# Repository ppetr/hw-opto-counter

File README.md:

# Universal IR optical, directional proximity detector/counter with TWI (I²C) interface

_*Disclaimer:* This is not an officially supported Google product._

The board uses two IR LEDs with a modulated signal (both either 38KHz or 56KHz,
depending on the receiver type) whose light reflects off objects in front of
the device into an IR receiver.

Using two LEDs allows to determine an approximate position (or direction of
movement) of an object in one dimension. Modulating the signal significantly
reduces interference from natural IR light sources.

The microcontroller
([ATtiny3224](https://www.microchip.com/en-us/product/attiny3224)) varies the
signal strength to compute the strength of the reflected signal using the
[binary search
algorithm](https://en.wikipedia.org/wiki/Binary_search_algorithm).

The measured values are made available through I²C (subordinate).

## Event counter

In addition to reporting current values of reflections from both LEDs, the
microcontroller also counts the number of times the reflection quickly changes
(which we call "events"). These events are defined using two parameters:

- [Exponential moving
  average](https://en.wikipedia.org/wiki/Exponential_smoothing) smoothing
  factor ("half-life"), which computes the baseline signal to compare against.
  The default value is half-life of 10s.
- Delta factor \[0..1\]. An event is triggered when the signal differs more
  than the delta factor from its exponential moving average.

There are the following event types that are counted independently:

1. Signal reflected from LED1 crosses the delta boundary and returns while
   LED2's signal remained within.
   ```
   LED1:  ___|‾‾‾|___
   LED2:  ___________
   ```
2. Similarly the other way around.
3. LED1's signal crossed outside the delta boundary followed by LED2's signal
   crossing outside. This captures the situation when an object is moving in
   the direction LED1->LED2.
   ```
   LED1:  __|‾‾‾|____
   LED2:  ____|‾‾‾|__
   ```
4. Similarly the other way around.

## Status

Development of a prototype.

## Contributions

Please see [Code of Conduct](docs/code-of-conduct.md) and [Contributing](docs/contributing.md).

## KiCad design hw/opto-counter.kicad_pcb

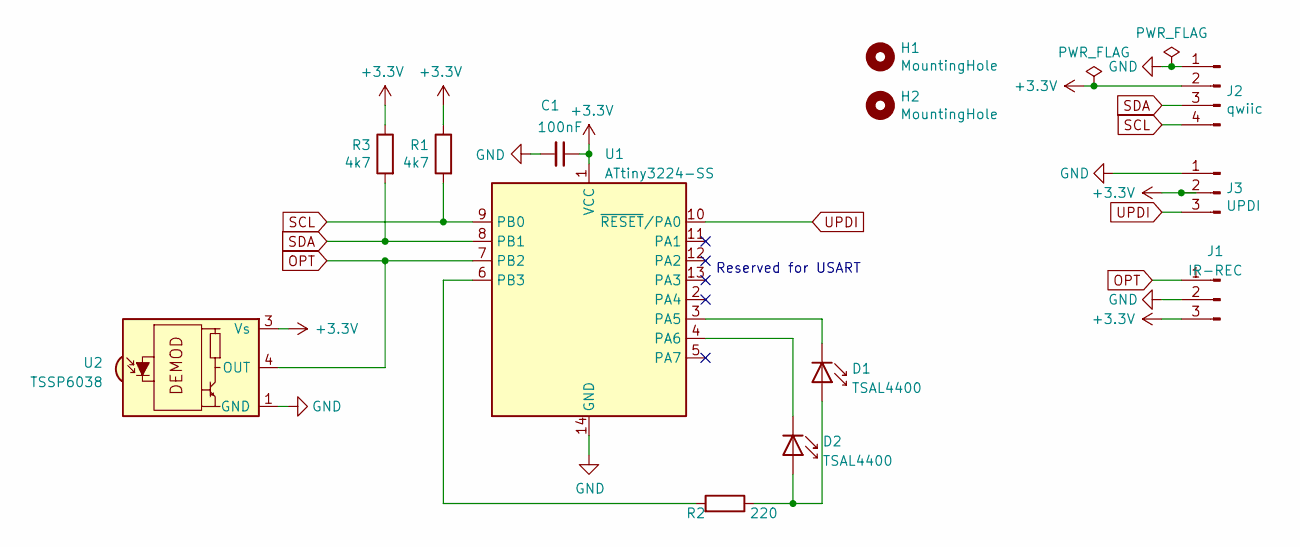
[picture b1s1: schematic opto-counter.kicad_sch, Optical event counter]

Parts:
C1: 100nF; C_1206_3216Metric_Pad1.33x1.80mm_HandSolder
D1, D2: TSAL4400; LED_D3.0mm_IRBlack
H1, H2: MountingHole; MountingHole_2.2mm_M2
J1: IR-REC; PinHeader_1x03_P2.54mm_Vertical
J2: qwiic; JST_XH_S4B-XH-A_1x04_P2.50mm_Horizontal
J3: UPDI; JST_XH_S3B-XH-A_1x03_P2.50mm_Horizontal
R1, R3: 4k7; R_1206_3216Metric_Pad1.30x1.75mm_HandSolder
R2: 220; R_1206_3216Metric_Pad1.30x1.75mm_HandSolder
U1: ATtiny3224-SS; SOIC-14_3.9x8.7mm_P1.27mm
U2: TSSP6038; TSS60xx

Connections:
+3V3: C1.1, J1.3, J2.2, J3.2, R1.1, R3.1, U1.1 (VCC), U2.3 (Vs)
GND: C1.2, J1.2, J2.1, J3.1, U1.14 (GND), U2.1 (GND)
unnamed: D1.2 (A), D2.2 (A), R2.1
unnamed: D1.1 (K), U1.3 (PA5)
unnamed: D2.1 (K), U1.4 (PA6)
unnamed: R2.2, U1.6 (PB3)
OPT: J1.1, U1.7 (PB2), U2.4 (OUT)
SCL: J2.4, R1.2, U1.9 (PB0)
SDA: J2.3, R3.2, U1.8 (PB1)
UPDI: J3.3, U1.10 (~RESET/PA0)

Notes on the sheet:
Reserved for USART

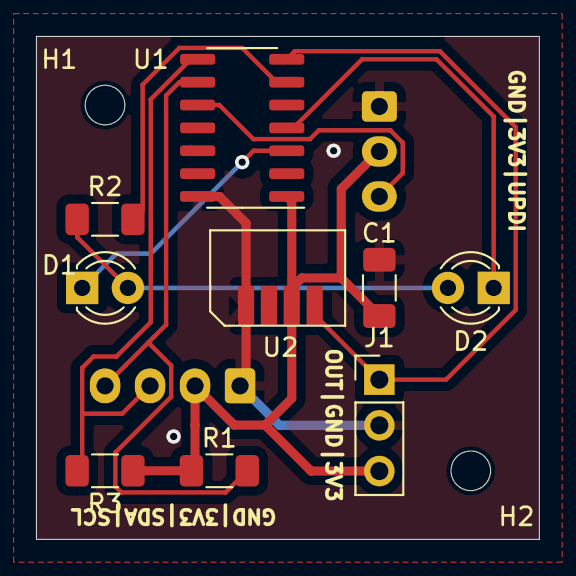
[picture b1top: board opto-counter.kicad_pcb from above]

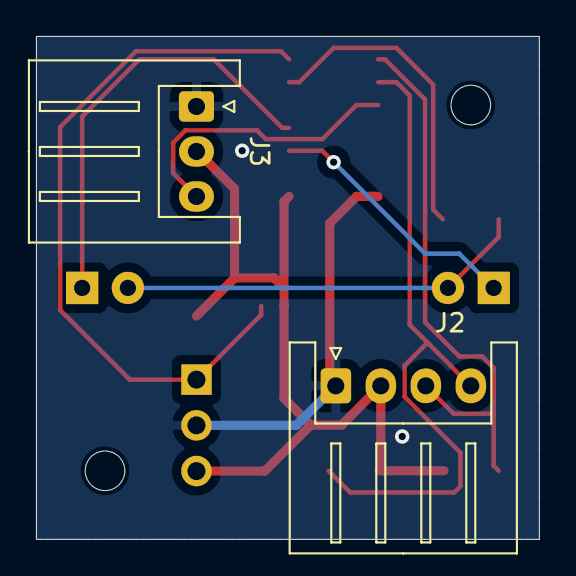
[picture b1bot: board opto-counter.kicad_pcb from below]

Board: 2 copper layers, 27.9 x 27.9 mm, 13 parts (2 on the bottom side), 10 nets.

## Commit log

2023-10-22 Initial (untested) prototype
2023-10-30 Remove temporary library `opto-counter-rescue`
    Also add forgotten `fp-lib-table` and small changes to the PCB.
2023-10-30 Old gerbers files for archiving
2023-10-30 Small improvements and fixes in the PCB, generated new gerbers files
2023-11-03 Use ATtiny1614-SS as the mCPU
    Actually, we're targetting to ATtiny3224, which should be pin
    compatible.
2023-11-03 Move the hardware design to `hw` and add a skeleton of the C software to `sw`
2023-11-04 Capitalize `make` variables and fix/clean up targets
2023-11-04 Remove gerbers and files that have been moved to `hw/`
    Update .gitignore
2023-11-04 Add README.md, the required license and corresponding docs
2023-11-04 Use ATtiny3224 as the mCPU in the schematic
2023-11-04 Add a footprint for TSSP60xx
    https://www.vishay.com/docs/82868/tssp960.pdf
2023-11-06 Set up compilation and the `main.cc` file for proper C++
    Also add `.clang-format`.
2023-11-24 Set the programmer to `jtag2updi`
2023-11-24 Configure the TCA0 to emit a test PWM signal.
2023-11-25 Configure the TCA0 counter using `constexpr` precomputed register values
2023-11-25 Fix the schematic to connect the led to the PB0 (WO0) PWM output of TCA
2023-11-27 Count a given number of pulses from TCA0 using TCB0
    This will allow waiting for the optical receiver a given number of PWM
    wave cycles.
2023-11-27 Add a helper type that represents a fixed point floating point number
    Also a few minor clean-ups.
2023-11-27 Move helper types to a `util.h` module
2023-11-28 Move the TCA0 and TCB0 code (the timers) to a separate module
    For some reasons the compilation breaks and `clkSel` becomes a higher
    value than expected (most likely 7 instead of 5). But the CC options to
    optimize the full final binary prevent that again.
2023-11-30 Implement a binary search algorithm feeding the PWM duty cycle
    The algorithm returns a value at which value an input pin changes its
    value.
2023-11-30 Add missing copyright headers
2023-11-30 Include `avr/signature.h` in `main.cc`
    See http://www.nongnu.org/avr-libc/user-manual/group__avr__signature.html.
2023-12-02 Add an unfinished TWI implementation
    It currently replies correctly only on the first read. Subsequent reads
    return garbled data.
    It's necessary to switch the TCA0 output pins so that the TWI0 ones
    become available.
2023-12-02 Working implemention of TWI
    The problem with the previous code was caused by checking the `RXACK`
    flag. The protocol doesn't require that and rather the flag can be set
    to NACK by previous, correct communication.
2023-12-02 Clean up the TWI implementation
    Ensure that all paths set the `SCTRLB` register value by expressing them
    using a function with a return value.
2023-12-02 Change the mCPU pins to match TWI
2023-12-03 Compile without exceptions
2023-12-03 Separate the implementation of a `TwiClient` from the mCPU's state machine
    `TwiClient` now receives a class that needs to implement methods that
    are called at various stages of communication.
2023-12-04 Implement a basic variant of `std::optional` for more type-safe code
2023-12-04 Use `FixedPointFraction` for values returned from `BinarySearch`
2023-12-04 Implement SMBus reading word registers
2023-12-04 Document a bit better a Quick command
2023-12-04 Update the PCB with the new pin assignments
2023-12-04 Implement the main functionality - measuring taken from both LEDs alternately
2023-12-05 Add a conversion function between different `FixedPointFraction` types
2023-12-06 Add the standard variants of `optional::operator*`
2023-12-06 Automatically convert to higher-precision `FixedPrecisionFraction`s
2023-12-06 Add auto-confersion of `FixedPointFraction` that with a static shift
2023-12-08 Small improvements of the PCB before producing prototype v2
2024-10-03 Some more work on fixing the PCB
2024-10-03 Properly reset the single-shot timer upon (re)starting
2024-10-03 Shift fraction bits only after casting to the new type
2024-10-03 Define a constant for the binary search not ready
2024-10-03 Add `const` to appropriate variables and fix a comment
2024-10-03 Update the ATtiny library
2026-06-09 Enable interrupts in `main` so that they can wake up the Sleep Controller
    Also make sure `OnInterrupt` calls process all pending events, not just
    one.
    See https://gemini.google.com/share/3b2ed1abc276

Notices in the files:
hw/opto-counter.kicad_sch:
Copyright 2023 Google LLC
Licensed under the Apache License, Version 2.0 (the \"License\").
